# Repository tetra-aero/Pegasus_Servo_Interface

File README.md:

# Pegasus_Servo_Interface
Pegaus servo interface

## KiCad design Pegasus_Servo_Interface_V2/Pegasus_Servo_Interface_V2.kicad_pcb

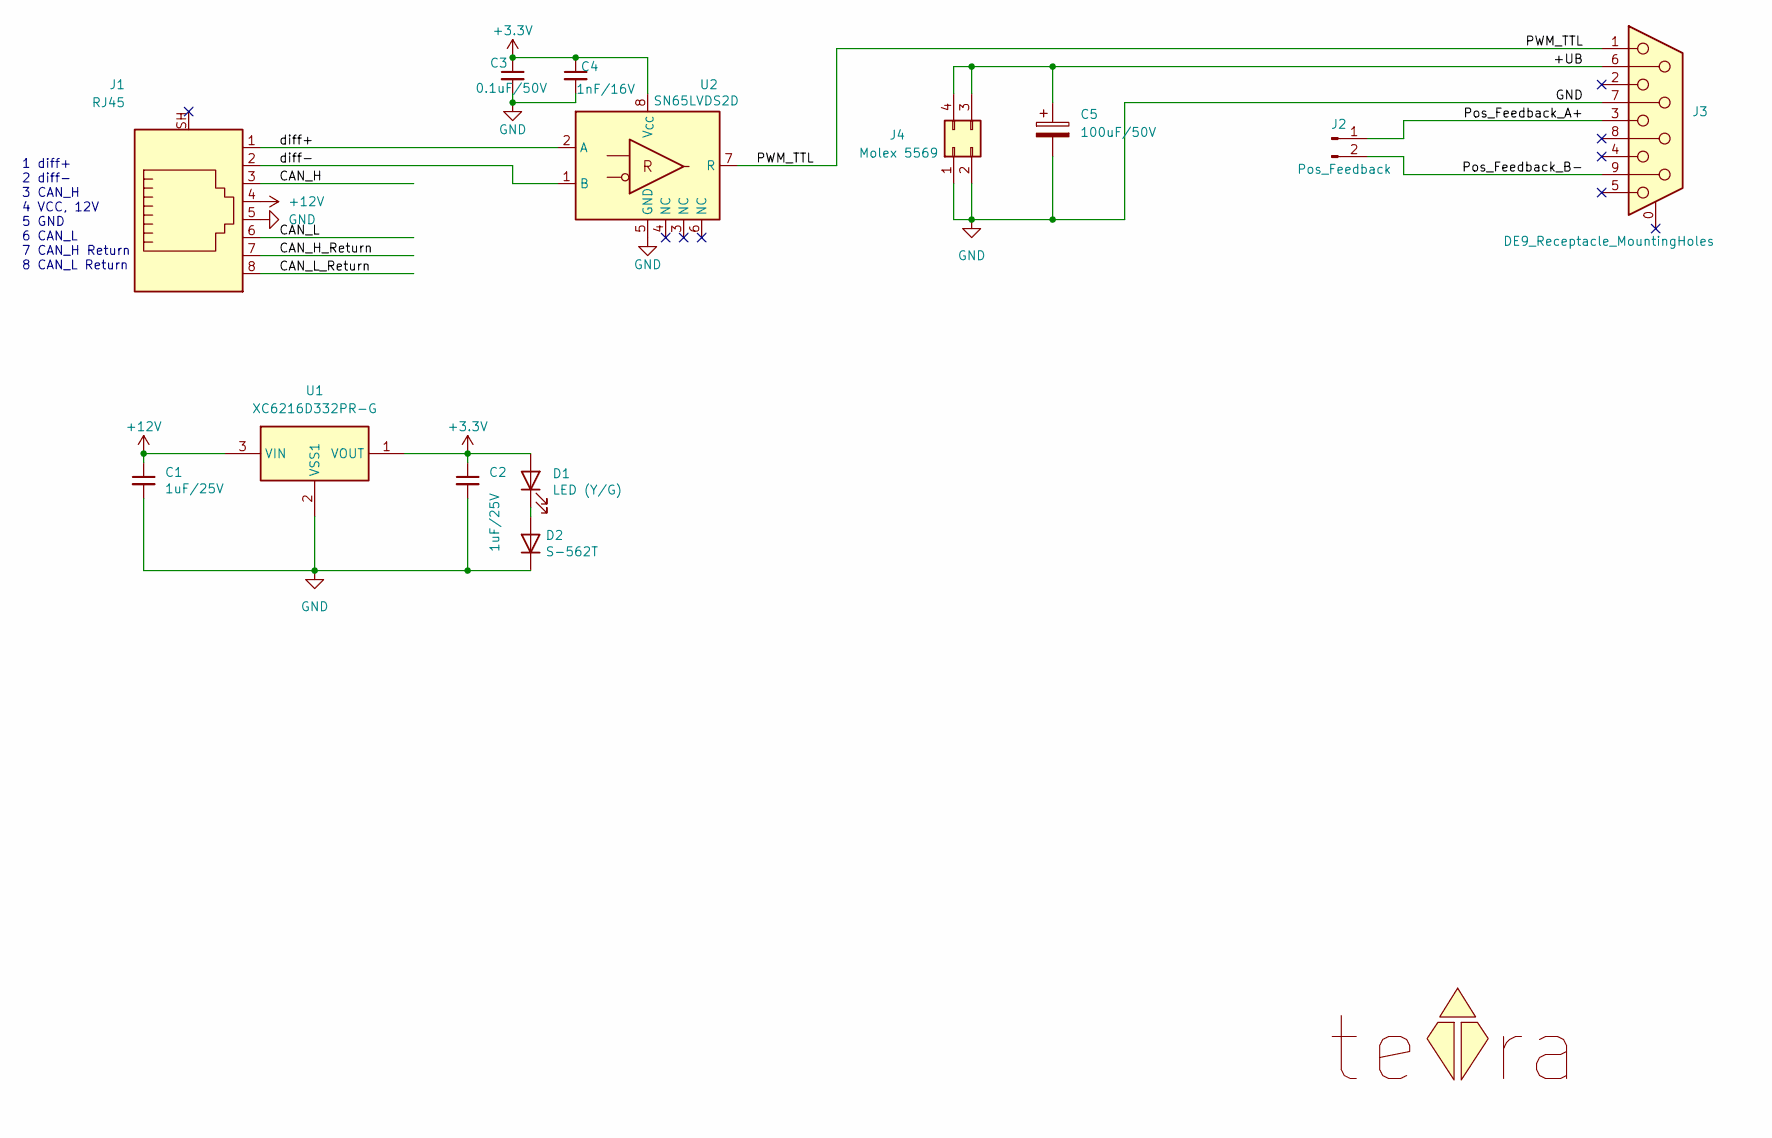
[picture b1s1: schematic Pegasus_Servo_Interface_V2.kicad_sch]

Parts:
C1, C2: 1uF/25V; C_0603_1608Metric; MPN CL10A105KA8NNNC
C3: 0.1uF/50V; C_0603_1608Metric; MPN CL10B104KB8NNWC
C4: 1nF/16V; C_0603_1608Metric; MPN C0603C102K4RECAUTO
C5: 100uF/50V; CP_Radial_D8.0mm_P5.00mm; MPN 50ZLH100MEFC8X11.5
D1: LED (Y/G); LED_0603_1608Metric; MPN LTST-C191KGKT
D2: S-562T; MPN S-562T
J1: RJ45; RJ45_Amphenol_RJHSE5380; MPN RJHSE-5380
J2: Pos_Feedback; PinHeader_1x02_P2.54mm_Vertical
J3: DE9_Receptacle_MountingHoles; DSUB-9_Male_Calendar_P2.77x2.84mm_MountingHoles3.1mm_24.99; MPN DE09S064HTLF
J4: Molex 5569; Molex_Mini-Fit_Jr_5569-04A2_2x02_P4.20mm_Horizontal; MPN 0026013115
LOGO1: teTra; teTra-LOGO
U1: XC6216D332PR-G; SOT-89-3; MPN XC6216D332PR-G
U2: SN65LVDS2D; SOIC-8_3.9x4.9mm_P1.27mm; MPN SN65LVDS2DR

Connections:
+3.3V: C2.1, C3.1, C4.1, D1.2 (A), U1.1 (VOUT), U2.8 (V_{CC})
+12V: C1.1, J1.4, U1.3 (VIN)
/+UB: C5.1, J3.6, J4.3, J4.4
/CAN_H: J1.3
/CAN_H_Return: J1.7
/CAN_L: J1.6
/CAN_L_Return: J1.8
/PWM_TTL: J3.1, U2.7 (R)
/Pos_Feedback_A+: J2.1, J3.3
/Pos_Feedback_B-: J2.2, J3.9
/diff+: J1.1, U2.2 (A)
/diff-: J1.2, U2.1 (B)
GND: C1.2, C2.2, C3.2, C4.2, C5.2, D2.1 (K), J1.5, J3.7, J4.1, J4.2, U1.2 (VSS1), U2.5 (GND)
unnamed: D1.1 (K), D2.2 (A)

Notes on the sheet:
1 diff+ 2 diff- 3 CAN_H 4 VCC, 12V 5 GND 6 CAN_L 7 CAN_H Return 8 CAN_L Return

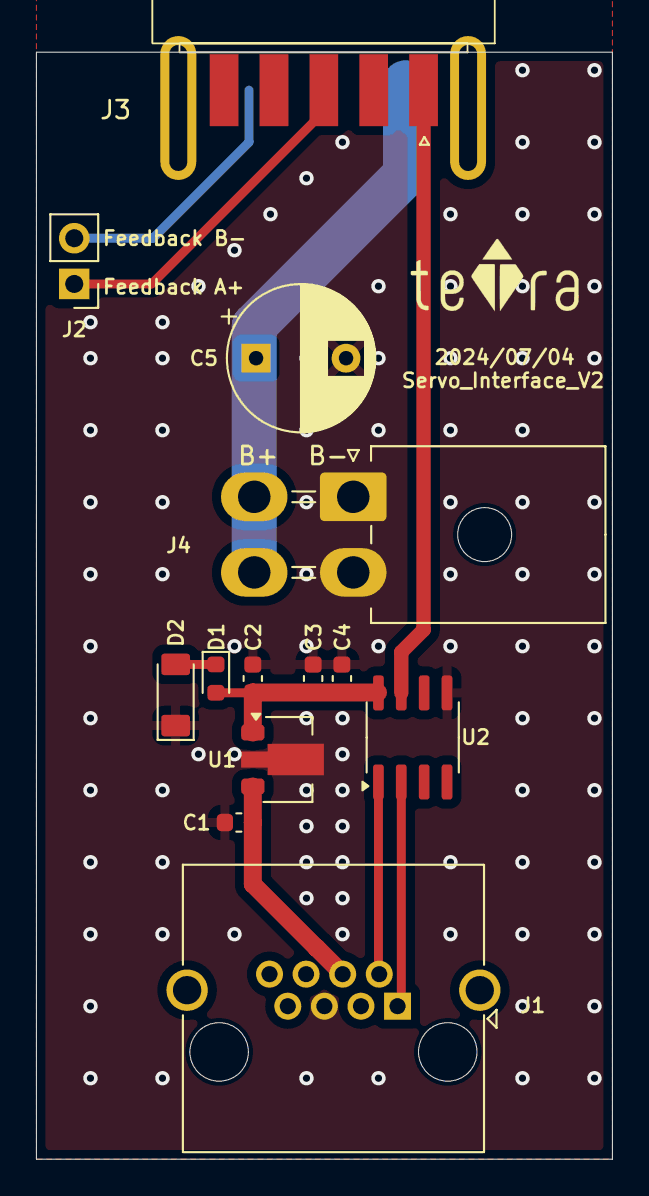
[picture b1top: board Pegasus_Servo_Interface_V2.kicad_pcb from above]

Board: 2 copper layers, 32.0 x 61.5 mm, 14 parts (0 on the bottom side), 10 nets.

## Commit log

2024-07-02 add pegasus servo interface v1
    add pegasus servo interface v1
2024-07-04 order v1
    order v1
2024-07-04 Change DSUB to plug DSUB
    Change DSUB to ESC interface board style direct plug DSUB
2024-07-04 Change the substrate thickness to 1.2mm
2024-07-04 order v2
    order v2
